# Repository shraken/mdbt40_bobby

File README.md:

# mdbt40_bobby

A simple break-out board in KiCad EDA for developing Nordic nRF51 BLE projects using the MDBT40 module.  Includes external 32.768 kHz watch crystal and components for internal DC/DC operation.  Breaks out 17 pins from the MDBT40 module for easy prototyping.

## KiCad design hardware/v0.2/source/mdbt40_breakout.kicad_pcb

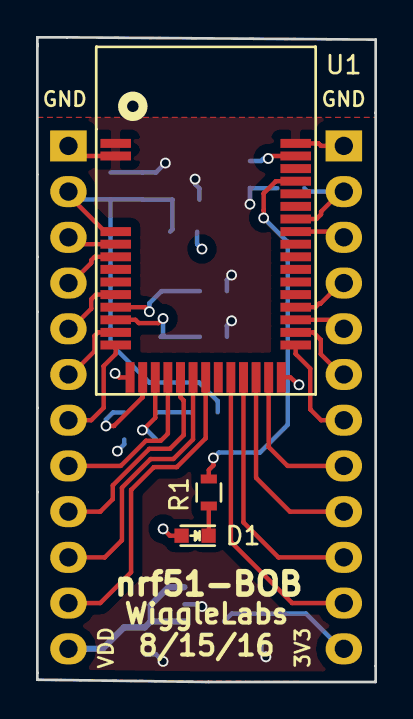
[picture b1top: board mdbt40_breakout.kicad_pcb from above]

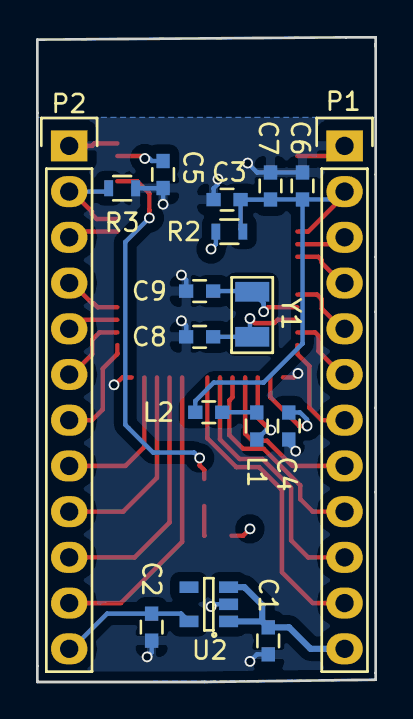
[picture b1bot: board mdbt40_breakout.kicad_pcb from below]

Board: 4 copper layers, 18.8 x 35.8 mm, 20 parts (17 on the bottom side), 30 nets.

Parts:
C1, C4, C6: 1uF; C_0603
C2: 100nF; C_0603
C3: 0.1uF; C_0603
C5: 47nF; C_0603
C7: 100pF; C_0603
C8, C9: 9pF; C_0603
D1: LED; LED_0603
L1: 10uH; C_0603
L2: 15nH; C_0603
P1, P2: CONN_01X12; Pin_Header_Straight_1x12
R1: 4.7k; R_0603
R2: 0R_NM; R_0603
R3: 12k; R_0603
U1: MDBT40
U2: TLV70033DDC; SOT-23-5
Y1: 32.768kHz; ABS07-LR-32.768kHz-6-1-T

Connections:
+3V3: C2.1, C4.1, D1.2, P2.12, R2.1, U1.14, U2.5
/AVDD: C3.1, C6.1, C7.1, L2.1, P1.2, R2.2, U1.3
/P0_00: P1.9, U1.17
/P0_01: P1.10, U1.18
/P0_02: P1.11, U1.19
/P0_04: P2.11, U1.21
/P0_05: P2.10, U1.22
/P0_06: P2.9, U1.23
/P0_07: P2.8, U1.24
/P0_08: P2.7, U1.26
/P0_09: P2.6, U1.27
/P0_10: P2.5, U1.28
/P0_11: P2.4, U1.29
/P0_19: R1.1, U1.39
/P0_21: P1.3, U1.4
/P0_22: P1.4, U1.5
/P0_25: P1.5, U1.8
/P0_28: P1.6, U1.11
/P0_29: P1.7, U1.12
/P0_30: P1.8, U1.16
/SWDCLK: P2.2, R3.2, U1.36
/SWDIO: P2.3, U1.35
GND: C1.2, C2.2, C3.2, C4.2, C5.1, C6.2, C7.2, C8.1, C9.1, P1.1, P2.1, R3.1, U1.1, U1.2, U1.13, U1.25, U1.42, U2.2
unnamed: C5.2, U1.41
unnamed: C8.2, U1.10, Y1.1
unnamed: C9.2, U1.9, Y1.2
unnamed: D1.1, R1.2
unnamed: L1.1, U1.15
unnamed: L1.2, L2.2
VDD: C1.1, P1.12, U2.1, U2.3

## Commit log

2016-10-08 first commit of v0.1 and v0.2
2016-10-09 add LICENSE file
